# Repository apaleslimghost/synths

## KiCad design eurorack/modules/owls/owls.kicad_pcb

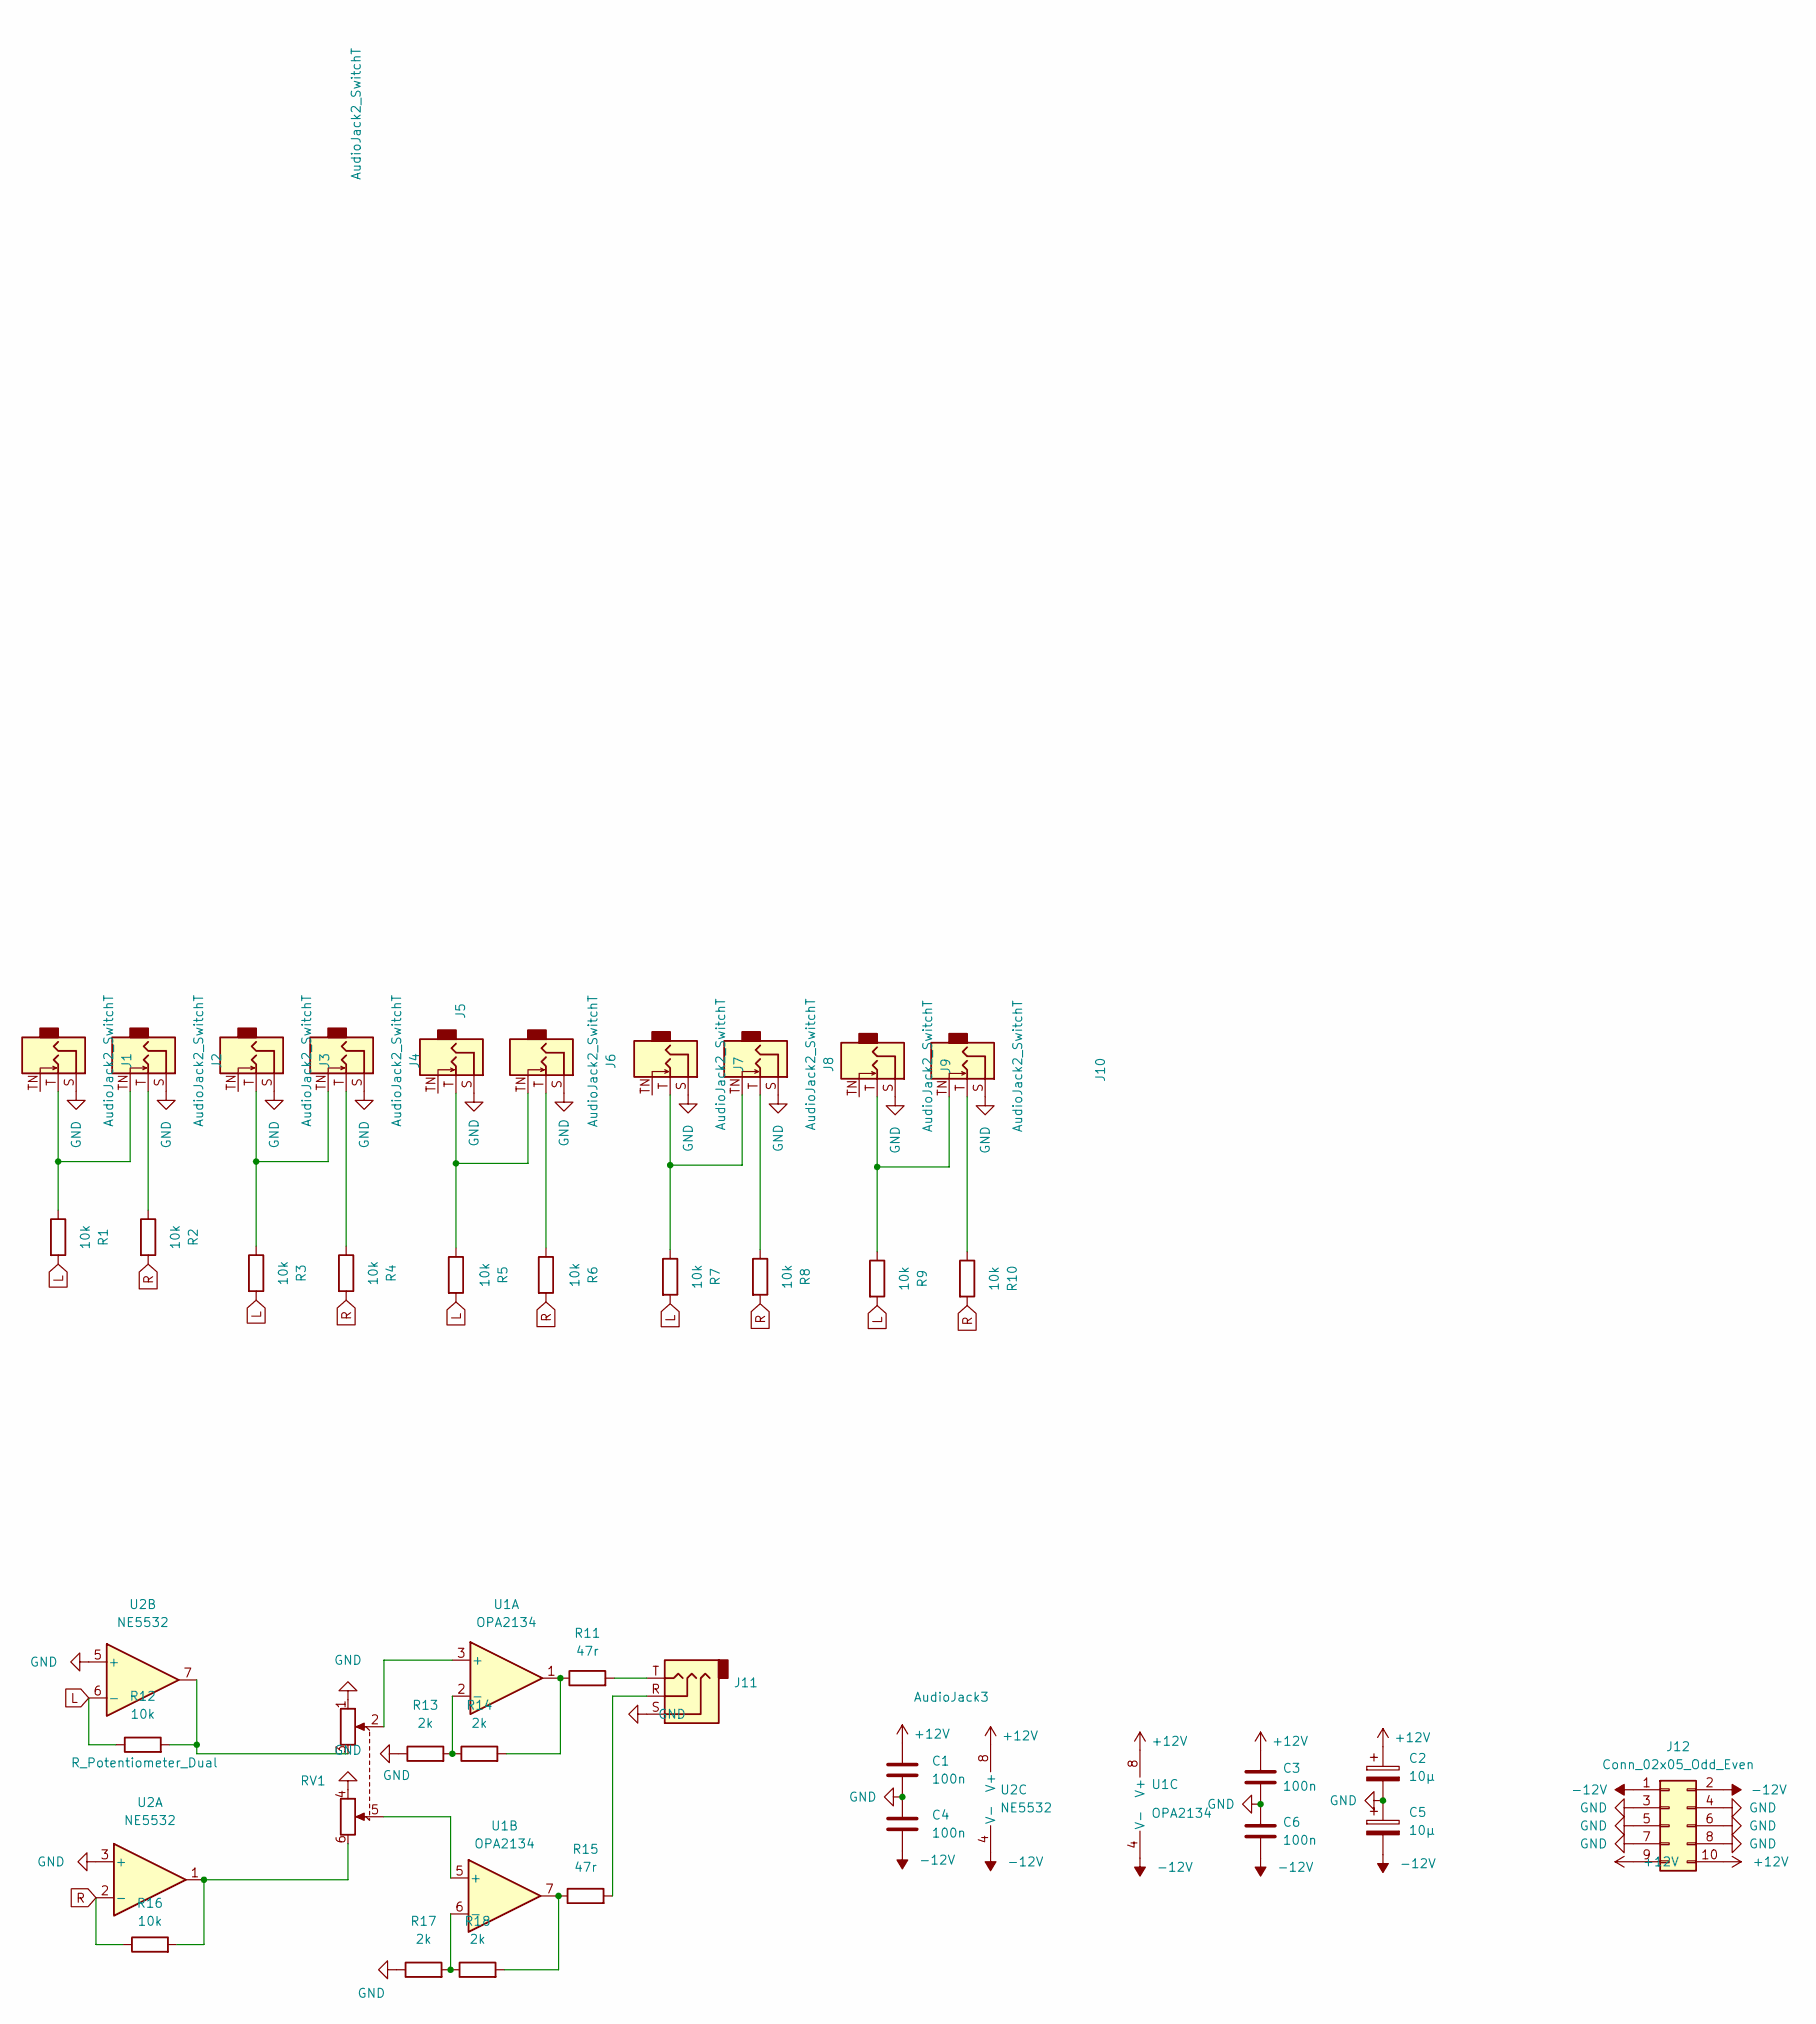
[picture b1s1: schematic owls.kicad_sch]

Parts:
C1, C3, C4, C6: 100n; C_0805_2012Metric_Pad1.18x1.45mm_HandSolder
C2, C5: 10μ; CP_Elec_5x4.5
J1, J2, J3, J4, J5, J6, J7, J8, J9, J10: AudioJack2_SwitchT; Jack_3.5mm_QingPu_WQP-PJ398SM_Vertical
J11: AudioJack3; Jack_3.5mm_QingPu_WQP-PJ366ST_Vertical
J12: Conn_02x05_Odd_Even; PinHeader_2x05_P2.54mm_Vertical_SMD
R1, R2, R3, R4, R5, R6, R7, R8, R9, R10, R12, R16: 10k; R_0805_2012Metric_Pad1.20x1.40mm_HandSolder
R11, R15: 47r; R_0805_2012Metric_Pad1.20x1.40mm_HandSolder
R13, R14, R17, R18: 2k; R_0805_2012Metric_Pad1.20x1.40mm_HandSolder
RV1: R_Potentiometer_Dual; Potentiometer_Alpha_RD902F-40-00D_Dual_Vertical
U1: OPA2134; SOIC-8_3.9x4.9mm_P1.27mm
U2: NE5532; SOIC-8_3.9x4.9mm_P1.27mm

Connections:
+12V: C1.1, C2.1, C3.1, J12.9, J12.10, U1.8 (V+), U2.8 (V+)
-12V: C4.2, C5.2, C6.2, J12.1, J12.2, U1.4 (V-), U2.4 (V-)
GND: C1.2, C2.2, C3.2, C4.1, C5.1, C6.1, J1.S, J2.S, J3.S, J4.S, J5.S, J6.S, J7.S, J8.S, J9.S, J10.S, J11.S, J12.3, J12.4, J12.5, J12.6, J12.7, J12.8, R13.1, R17.1, RV1.1, RV1.4, U2.3 (+), U2.5 (+)
L: R1.2, R3.2, R5.2, R7.2, R9.2, R12.1, U2.6 (-)
unnamed: J1.T, J2.TN, R1.1
unnamed: J2.T, R2.1
unnamed: J3.T, J4.TN, R3.1
unnamed: J4.T, R4.1
unnamed: J5.T, J6.TN, R5.1
unnamed: J6.T, R6.1
unnamed: J7.T, J8.TN, R7.1
unnamed: J8.T, R8.1
unnamed: J10.T, R10.1
unnamed: J9.T, J10.TN, R9.1
unnamed: J11.R, R15.2
unnamed: J11.T, R11.2
unnamed: R11.1, R14.2, U1.1
unnamed: R12.2, RV1.3, U2.7
unnamed: R13.2, R14.1, U1.2 (-)
unnamed: R15.1, R18.2, U1.7
unnamed: R16.2, RV1.6, U2.1
unnamed: R17.2, R18.1, U1.6 (-)
unnamed: RV1.2, U1.3 (+)
unnamed: RV1.5, U1.5 (+)
R: R2.2, R4.2, R6.2, R8.2, R10.2, R16.1, U2.2 (-)

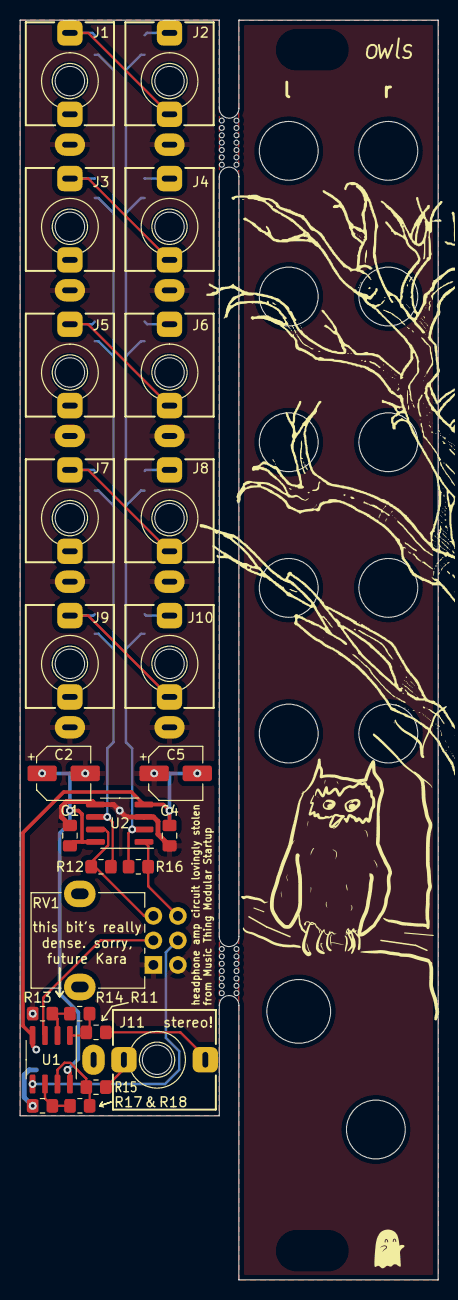
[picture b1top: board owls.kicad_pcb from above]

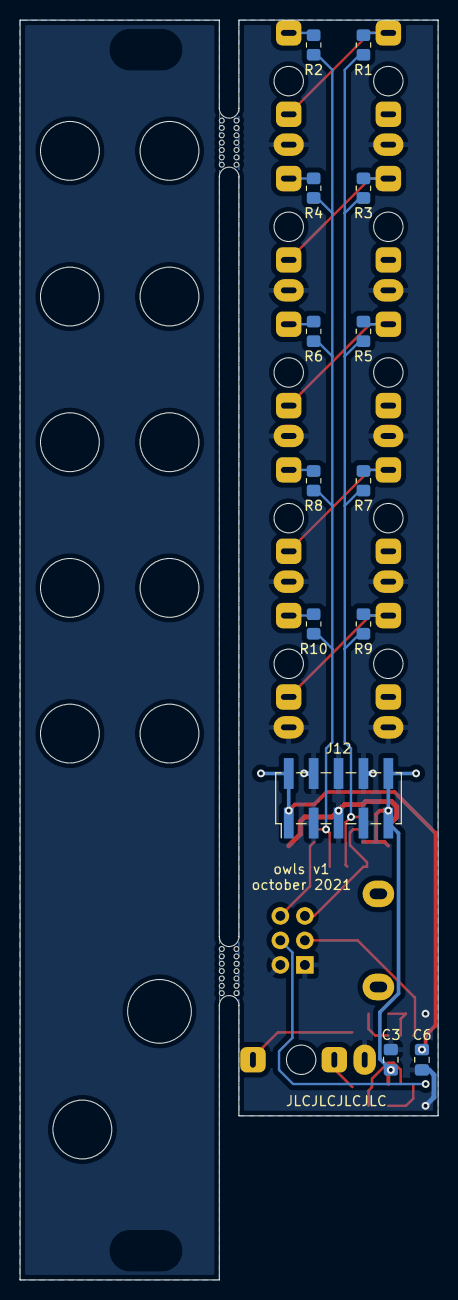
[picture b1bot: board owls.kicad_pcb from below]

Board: 2 copper layers, 42.6 x 128.5 mm, 41 parts (13 on the bottom side), 25 nets.

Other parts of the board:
mouse-bite-2mm-slot, mouse-bite-2mm-slot#2: VAL**; mousebite-2x5mm

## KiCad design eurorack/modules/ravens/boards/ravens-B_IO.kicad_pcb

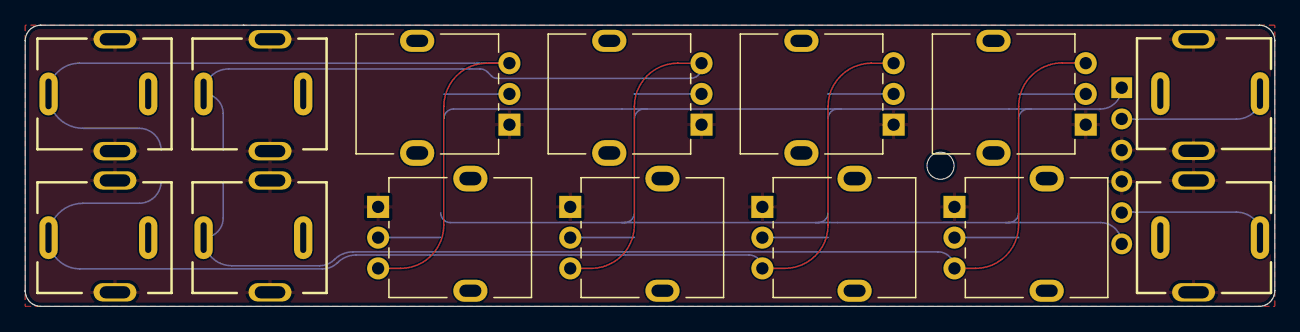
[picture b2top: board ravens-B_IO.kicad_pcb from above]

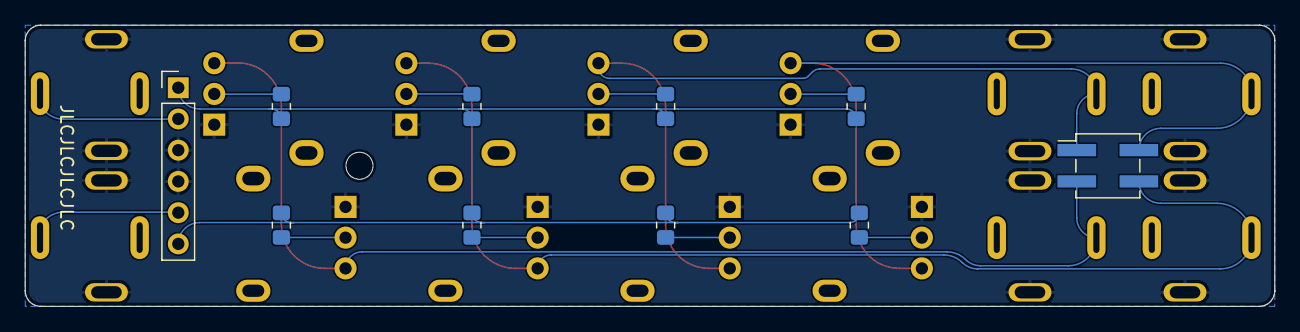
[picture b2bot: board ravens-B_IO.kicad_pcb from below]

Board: 2 copper layers, 101.6 x 22.9 mm, 26 parts (10 on the bottom side), 17 nets.

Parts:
B_IO: Board
H1: MountingHole; MountingHole_2.2mm_M2
J2, J3, J4, J5, J6, J7: AudioJack2_SwitchT; Jack_3.5mm_QingPu_WQP-PJ301BM_Vertical
J8: Conn_01x06_Pin; PinHeader_1x06_P2.54mm_Vertical
J12: Conn_01x04_Pin; PinHeader_2x02_P2.54mm_Vertical_SMD
R1, R2, R3, R4, R5, R6, R7, R8: 100k; R_0805_2012Metric_Pad1.20x1.40mm_HandSolder
RV1, RV2, RV3, RV4, RV5, RV6, RV7, RV8: R_Potentiometer; Potentiometer_Alpha_RD901F-40-00D_Single_Vertical

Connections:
Board_0-Bus A front: J8.1, R1.2, R3.2, R5.2, R7.2
Board_0-Bus B front: J8.6, R2.2, R4.2, R6.2, R8.2
Board_0-GND: J2.S, J3.S, J4.S, J5.S, J6.S, J7.S, J8.3, J8.4, RV1.1, RV2.1, RV3.1, RV4.1, RV5.1, RV6.1, RV7.1, RV8.1
Board_0-In 1: J2.T, J12.2, RV1.3, RV2.3
Board_0-In 2: J3.T, J12.1, RV3.3, RV4.3
Board_0-In 3: J4.T, J12.4, RV5.3, RV6.3
Board_0-In 4: J5.T, J12.3, RV7.3, RV8.3
Board_0-Net-(R1-Pad1): R1.1, RV1.2
Board_0-Net-(R2-Pad1): R2.1, RV2.2
Board_0-Net-(R3-Pad1): R3.1, RV3.2
Board_0-Net-(R4-Pad1): R4.1, RV4.2
Board_0-Net-(R5-Pad1): R5.1, RV5.2
Board_0-Net-(R6-Pad1): R6.1, RV6.2
Board_0-Net-(R7-Pad1): R7.1, RV7.2
Board_0-Net-(R8-Pad1): R8.1, RV8.2
Board_0-Out A front: J6.T, J8.2
Board_0-Out B front: J7.T, J8.5

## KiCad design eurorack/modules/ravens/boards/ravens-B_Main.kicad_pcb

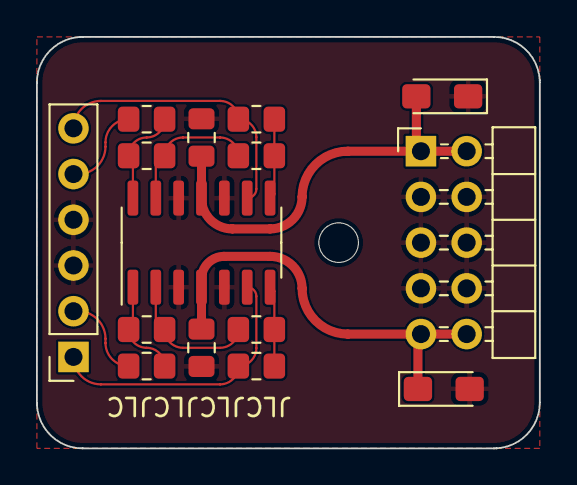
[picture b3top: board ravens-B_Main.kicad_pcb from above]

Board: 2 copper layers, 27.9 x 22.9 mm, 17 parts (0 on the bottom side), 13 nets.

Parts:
B_Main: Board
C1, C2: C_Polarized; CP_EIA-3216-18_Kemet-A_Pad1.58x1.35mm_HandSolder
C3, C4: C; C_0805_2012Metric_Pad1.18x1.45mm_HandSolder
H2: MountingHole; MountingHole_2.2mm_M2
J1: Conn_02x05_Odd_Even; PinHeader_2x05_P2.54mm_Horizontal
J9: Conn_01x06_Socket; PinSocket_1x06_P2.54mm_Vertical
R9, R10, R11, R14, R15, R16: 100k; R_0805_2012Metric_Pad1.20x1.40mm_HandSolder
R12, R13: 1k; R_0805_2012Metric_Pad1.20x1.40mm_HandSolder
U1: TL074; SOIC-14_3.9x8.7mm_P1.27mm

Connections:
Board_0-+12V: C1.1, C3.1, J1.9, J1.10, U1.4 (V+)
Board_0--12V: C2.2, C4.2, J1.1, J1.2, U1.11 (V-)
Board_0-Bus A back: J9.1, R9.1, U1.6 (-)
Board_0-Bus B back: J9.6, R16.1, U1.9 (-)
Board_0-GND1: C1.2, C2.1, C3.2, C4.1, J1.3, J1.4, J1.5, J1.6, J1.7, J1.8, J9.3, J9.4, U1.3 (+), U1.5 (+), U1.10 (+), U1.12 (+)
Board_0-Net-(R10-Pad1): R9.2, R10.1, U1.7
Board_0-Net-(R11-Pad2): R11.2, R12.1, U1.1
Board_0-Net-(R13-Pad1): R13.1, R15.2, U1.14
Board_0-Net-(R14-Pad1): R14.1, R16.2, U1.8
Board_0-Net-(U1A--): R10.2, R11.1, U1.2 (-)
Board_0-Net-(U1D--): R14.2, R15.1, U1.13 (-)
Board_0-Out A back: J9.2, R12.2
Board_0-Out B back: J9.5, R13.2

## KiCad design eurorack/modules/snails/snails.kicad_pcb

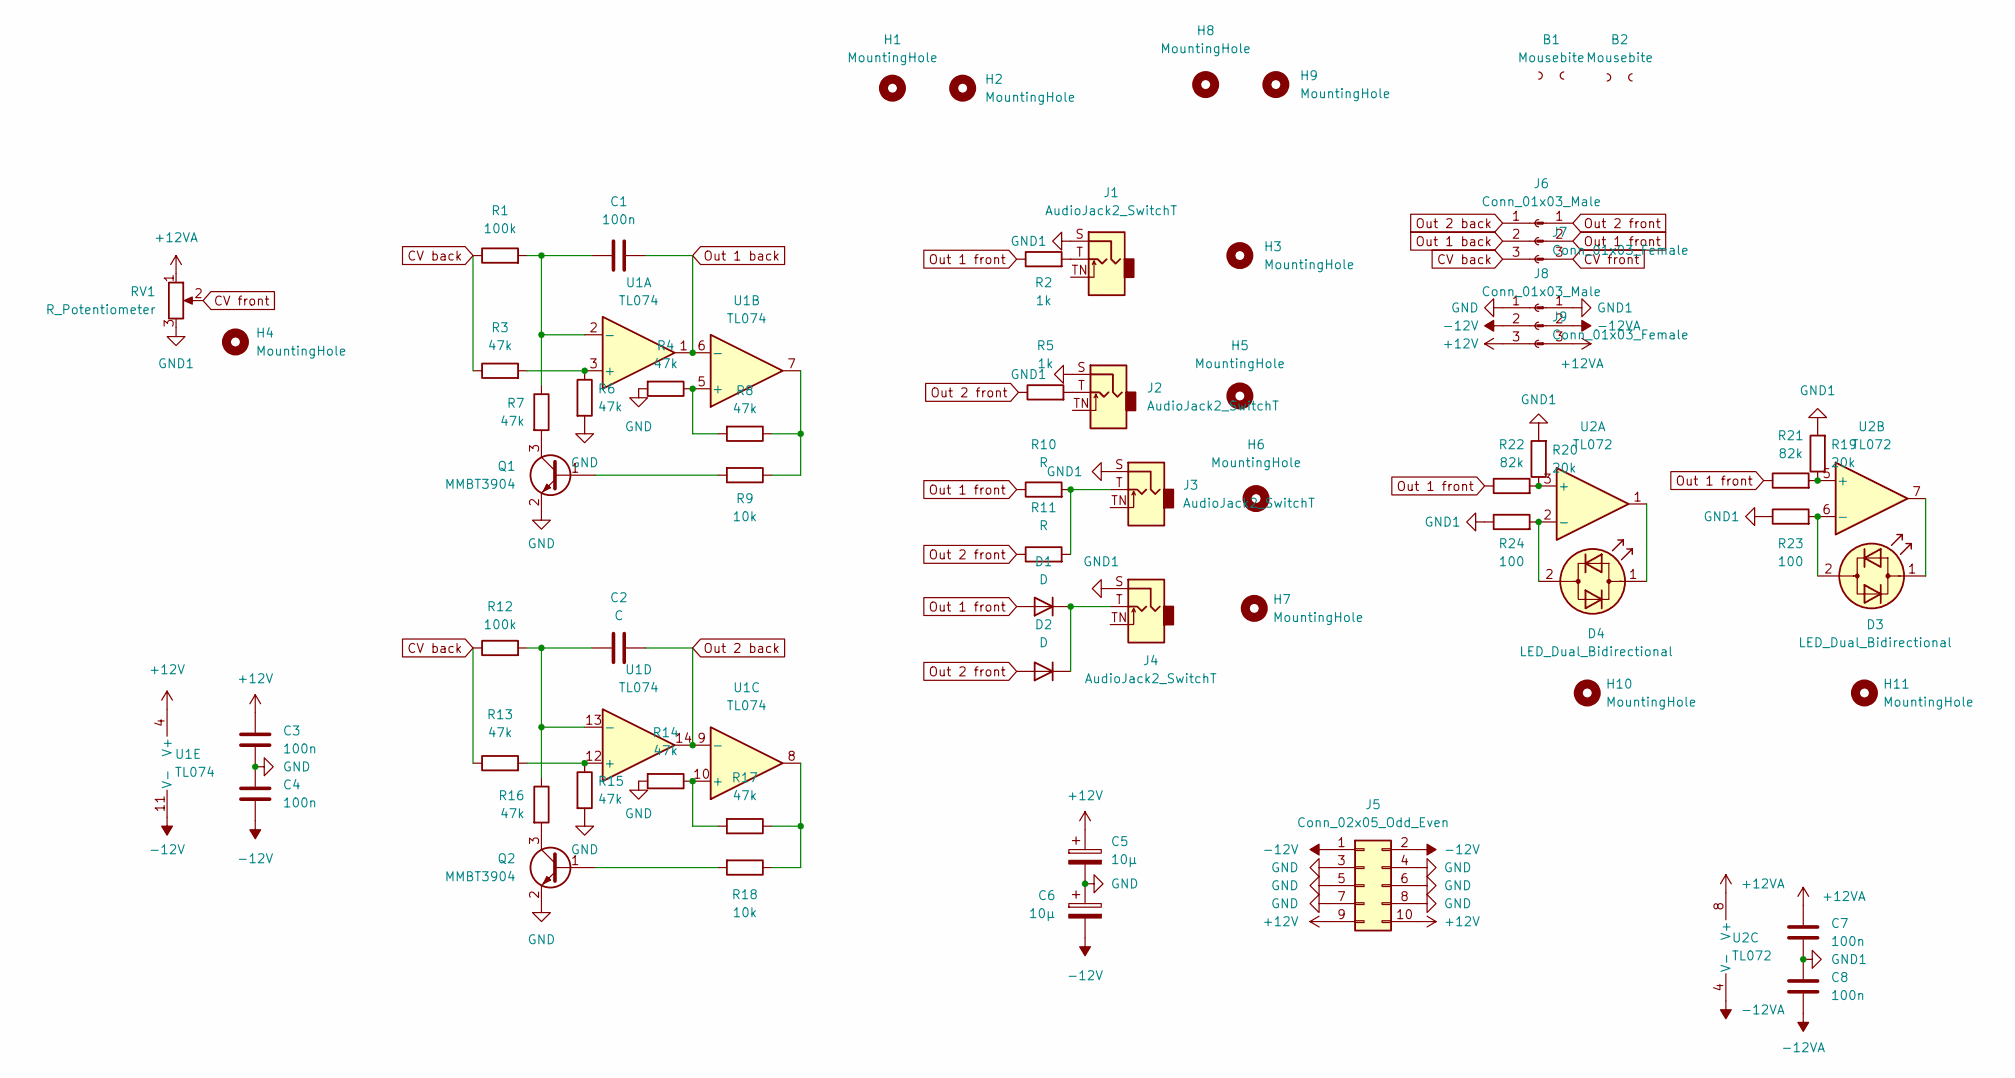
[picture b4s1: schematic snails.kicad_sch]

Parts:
B1, B2: Mousebite; mousebite-2.54x5.08mm
C1, C3, C4, C7, C8: 100n; C_0805_2012Metric_Pad1.18x1.45mm_HandSolder
C2: C; C_0805_2012Metric_Pad1.18x1.45mm_HandSolder
C5, C6: 10μ; CP_Elec_5x5.9
D1, D2: D; D_0805_2012Metric_Pad1.15x1.40mm_HandSolder
D3, D4: LED_Dual_Bidirectional; LED_D3.0mm_FlatTop
H1, H2: MountingHole; MountingHole_2.2mm_M2
H3, H5, H6, H7: MountingHole; hole 6mm (jack panel)
H4: MountingHole; hole 6.5mm (potentiometer panel)
H8, H9: MountingHole; eurorack panel mounting slot
H10, H11: MountingHole; hole 3mm (below jack)
J1, J2, J3, J4: AudioJack2_SwitchT; Jack_3.5mm_QingPu_WQP-PJ301BM_Vertical
J5: Conn_02x05_Odd_Even; PinHeader_2x05_P2.54mm_Vertical
J6, J8: Conn_01x03_Male; PinHeader_1x03_P2.54mm_Vertical
J7, J9: Conn_01x03_Female; PinSocket_1x03_P2.54mm_Vertical
Q1, Q2: MMBT3904; SOT-23
R1, R12: 100k; R_0805_2012Metric_Pad1.20x1.40mm_HandSolder
R2, R5: 1k; R_0805_2012Metric_Pad1.20x1.40mm_HandSolder
R3, R4, R6, R7, R8, R13, R14, R15, R16, R17: 47k; R_0805_2012Metric_Pad1.20x1.40mm_HandSolder
R9, R18: 10k; R_0805_2012Metric_Pad1.20x1.40mm_HandSolder
R10, R11: R; R_0805_2012Metric_Pad1.20x1.40mm_HandSolder
R19, R20: 20k; R_0805_2012Metric_Pad1.20x1.40mm_HandSolder
R21, R22: 82k; R_0805_2012Metric_Pad1.20x1.40mm_HandSolder
R23, R24: 100; R_0805_2012Metric_Pad1.20x1.40mm_HandSolder
RV1: R_Potentiometer; Potentiometer_Alpha_RD901F-40-00D_Single_Vertical
U1: TL074; SOIC-14_3.9x8.7mm_P1.27mm
U2: TL072; SOT-23-8

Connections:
+12V: C3.1, C5.1, J5.9, J5.10, J9.3, U1.4 (V+)
+12VA: C7.1, J8.3, RV1.1, U2.8 (V+)
-12V: C4.2, C6.2, J5.1, J5.2, J9.2, U1.11 (V-)
-12VA: C8.2, J8.2, U2.4 (V-)
CV back: J7.3, R1.1, R3.1, R12.1, R13.1
CV front: J6.3, RV1.2
GND: C3.2, C4.1, C5.2, C6.1, J5.3, J5.4, J5.5, J5.6, J5.7, J5.8, J9.1, Q1.2 (E), Q2.2 (E), R4.2, R6.2, R14.2, R15.2
GND1: C7.2, C8.1, J1.S, J2.S, J3.S, J4.S, J8.1, R19.2, R20.2, R23.1, R24.1, RV1.3
unnamed: C1.1, R1.2, R7.1, U1.2 (-)
unnamed: C2.1, R12.2, R16.1, U1.13 (-)
unnamed: D1.1 (K), D2.1 (K), J4.T
unnamed: D3.1 (KA), U2.7
unnamed: D3.2 (AK), R23.2, U2.6 (-)
unnamed: D4.1 (KA), U2.1
unnamed: D4.2 (AK), R24.2, U2.2 (-)
unnamed: J1.T, R2.2
unnamed: J2.T, R5.2
unnamed: J3.T, R10.2, R11.2
unnamed: Q1.1 (B), R9.2
unnamed: Q1.3 (C), R7.2
unnamed: Q2.1 (B), R18.2
unnamed: Q2.3 (C), R16.2
unnamed: R3.2, R6.1, U1.3 (+)
unnamed: R4.1, R8.2, U1.5 (+)
unnamed: R8.1, R9.1, U1.7
unnamed: R13.2, R15.1, U1.12 (+)
unnamed: R14.1, R17.2, U1.10 (+)
unnamed: R17.1, R18.1, U1.8
unnamed: R19.1, R21.2, U2.5 (+)
unnamed: R20.1, R22.2, U2.3 (+)
Out 1 back: C1.2, J7.2, U1.1, U1.6 (-)
Out 1 front: D1.2 (A), J6.2, R2.1, R10.1, R21.1, R22.1
Out 2 back: C2.2, J7.1, U1.9 (-), U1.14
Out 2 front: D2.2 (A), J6.1, R5.1, R11.1

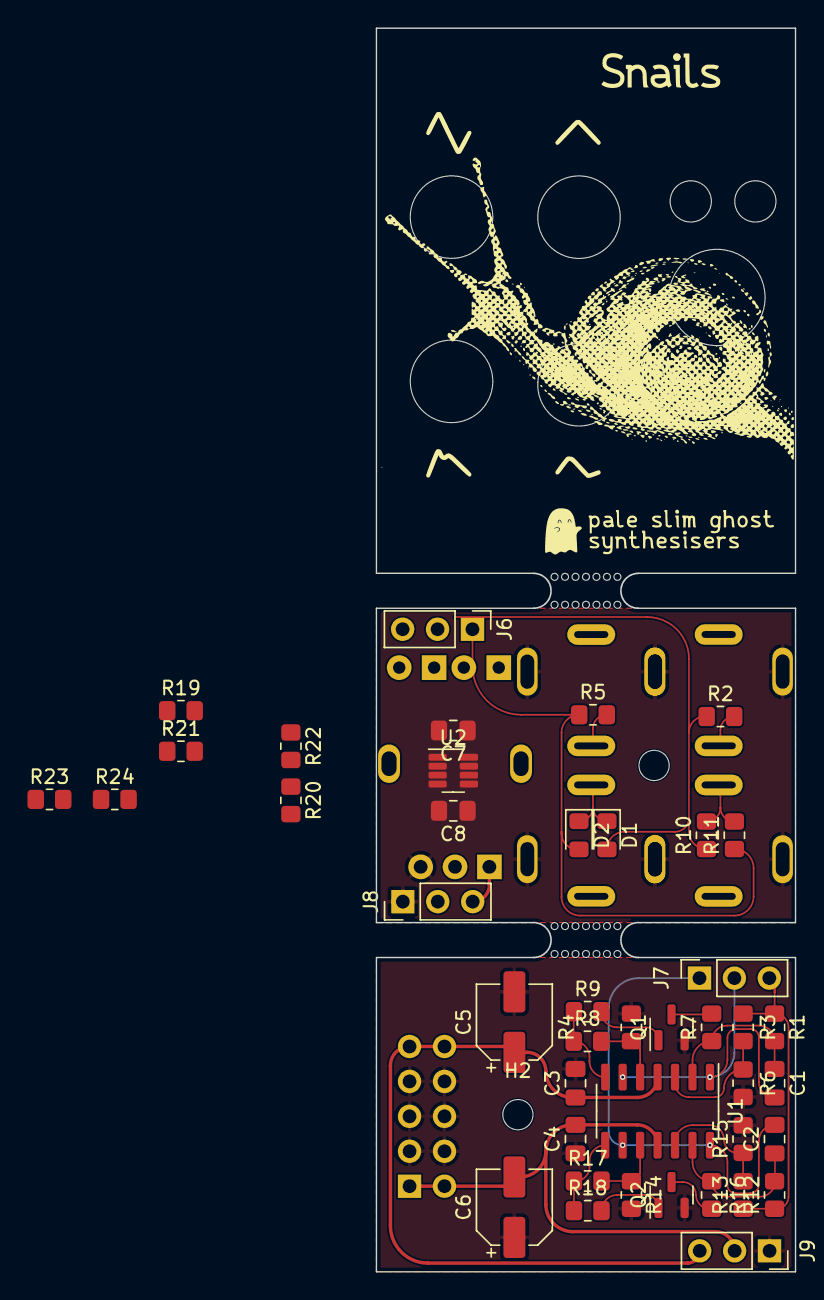
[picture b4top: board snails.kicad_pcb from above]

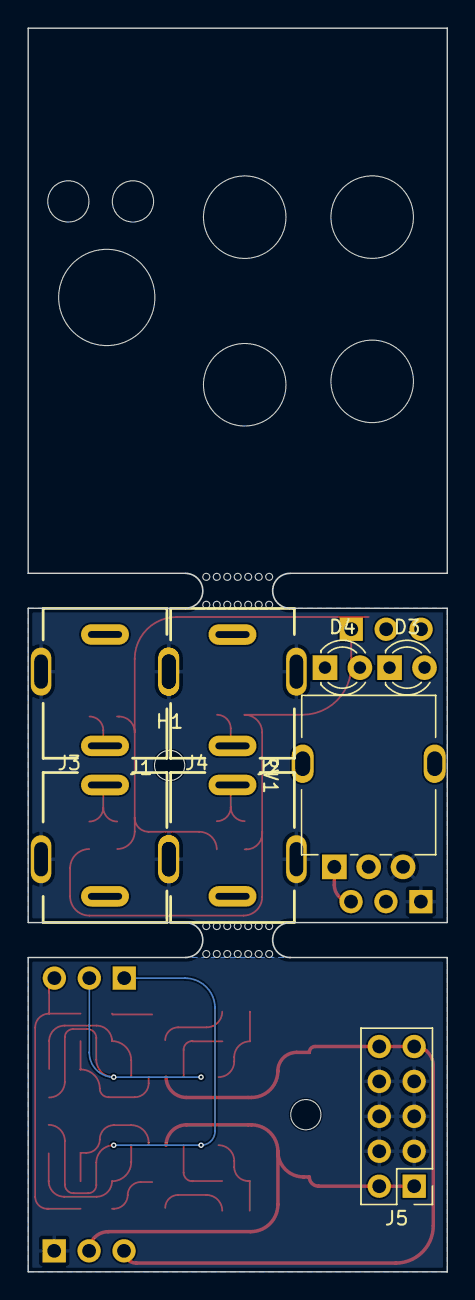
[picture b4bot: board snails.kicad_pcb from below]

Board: 2 copper layers, 30.5 x 90.4 mm, 63 parts (12 on the bottom side), 34 nets.

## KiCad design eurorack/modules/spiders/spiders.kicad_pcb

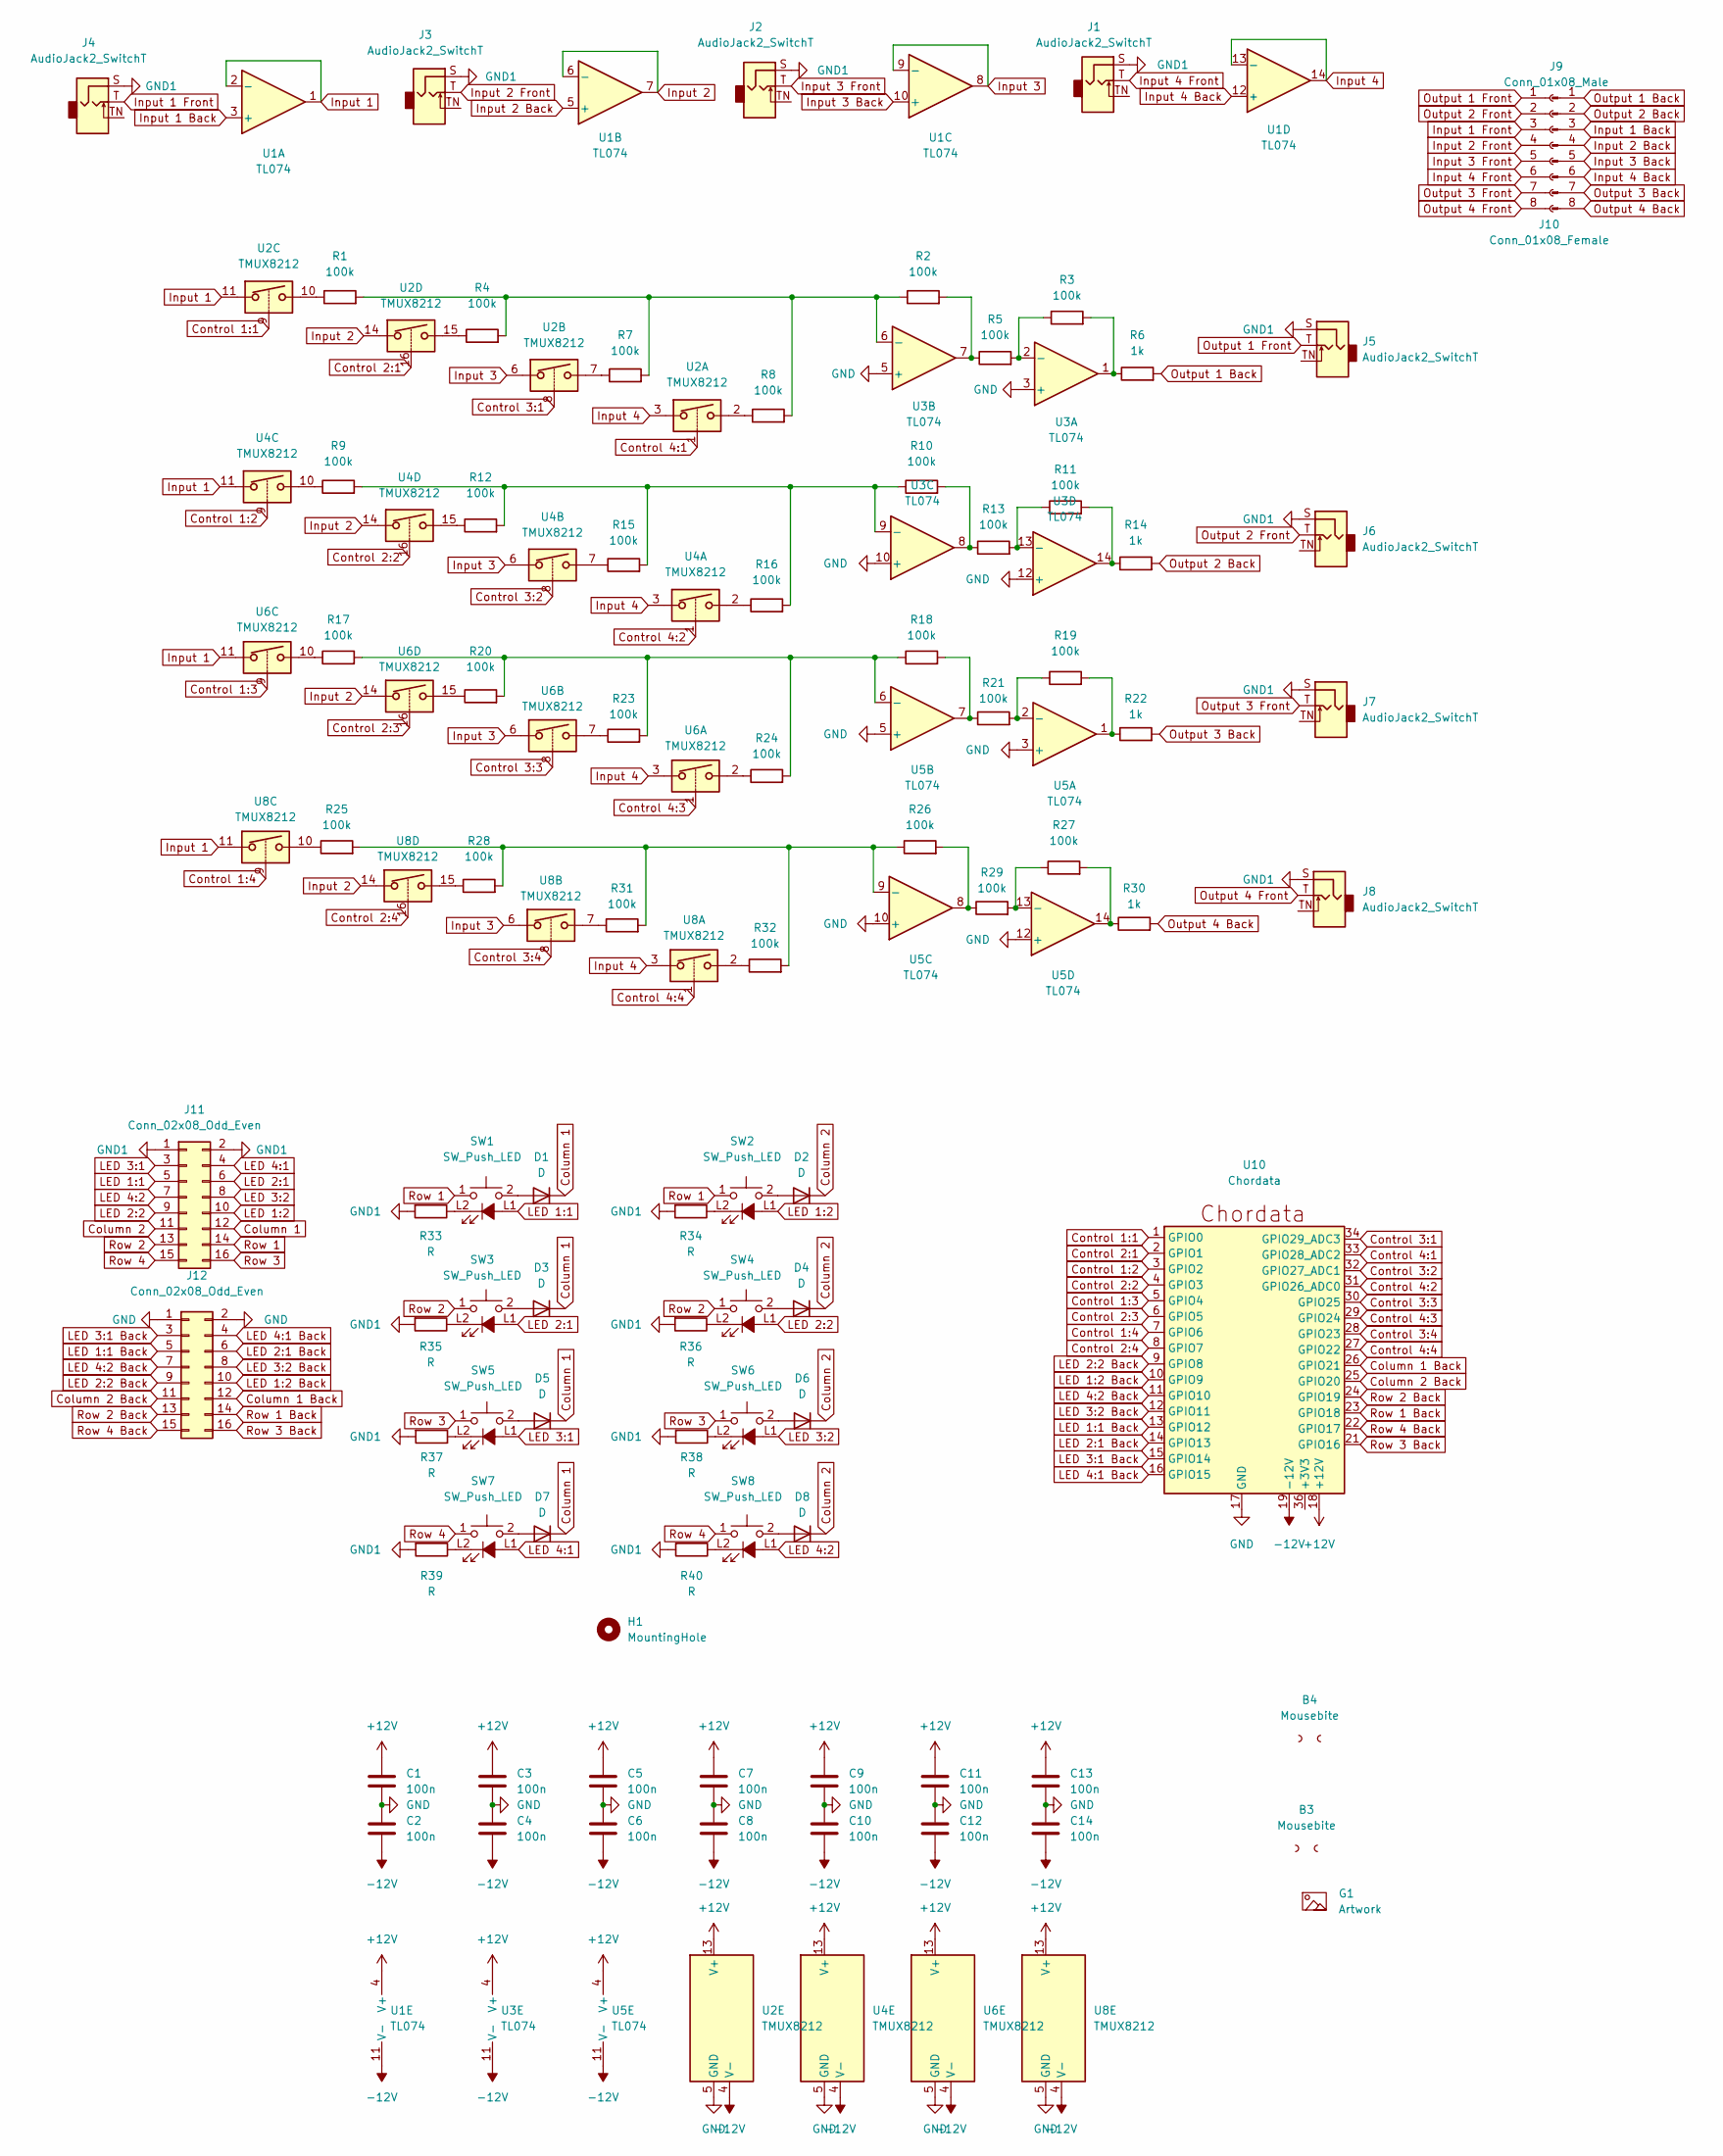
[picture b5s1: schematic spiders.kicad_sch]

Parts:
B3, B4: Mousebite; mousebite-2.54x5.08mm
C1, C2, C3, C4, C5, C6, C7, C8, C9, C10, C11, C12, C13, C14: 100n; C_0805_2012Metric
D1, D2, D3, D4, D5, D6, D7, D8: D; D_SOD-323_HandSoldering
G1: Artwork
H1: MountingHole; MountingHole_2.2mm_M2
J1, J2, J3, J4, J5, J6, J7, J8: AudioJack2_SwitchT; Jack_3.5mm_QingPu_WQP-PJ398SM_Vertical
J9: Conn_01x08_Male; PinHeader_1x08_P2.54mm_Vertical
J10: Conn_01x08_Female; PinSocket_1x08_P2.54mm_Vertical
J11: Conn_02x08_Odd_Even; PinSocket_2x08_P2.54mm_Vertical
J12: Conn_02x08_Odd_Even; PinHeader_2x08_P2.54mm_Vertical
R1, R2, R3, R4, R5, R7, R8, R9, R10, R11, R12, R13, R15, R16, R17, R18, R19, R20, R21, R23, R24, R25, R26, R27, R28, R29, R31, R32: 100k; R_0805_2012Metric
R6, R14, R22, R30: 1k; R_0805_2012Metric
R33, R34, R35, R36, R37, R38, R39, R40: R; R_0805_2012Metric
SW1, SW2, SW3, SW4, SW5, SW6, SW7, SW8: SW_Push_LED; PB01-109TL
U1, U3, U5: TL074; TSOT-23-14
U2, U4, U6, U8: TMUX8212; TSSOP-16_4.4x5mm_P0.65mm
U10: Chordata

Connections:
+12V: C1.1, C3.1, C5.1, C7.1, C9.1, C11.1, C13.1, U1.4 (V+), U2.13 (V+), U3.4 (V+), U4.13 (V+), U5.4 (V+), U6.13 (V+), U8.13 (V+), U10.18 (+12V)
-12V: C2.2, C4.2, C6.2, C8.2, C10.2, C12.2, C14.2, U1.11 (V-), U2.4 (V-), U3.11 (V-), U4.4 (V-), U5.11 (V-), U6.4 (V-), U8.4 (V-), U10.19 (-12V)
Column 1: D1.1 (K), D3.1 (K), D5.1 (K), D7.1 (K), J11.12
Column 1 Back: J12.12, U10.26 (GPIO21)
Column 2: D2.1 (K), D4.1 (K), D6.1 (K), D8.1 (K), J11.11
Column 2 Back: J12.11, U10.25 (GPIO20)
Control 1:1: U2.9, U10.1 (GPIO0)
Control 1:2: U4.9, U10.3 (GPIO2)
Control 1:3: U6.9, U10.5 (GPIO4)
Control 1:4: U8.9, U10.7 (GPIO6)
Control 2:1: U2.16, U10.2 (GPIO1)
Control 2:2: U4.16, U10.4 (GPIO3)
Control 2:3: U6.16, U10.6 (GPIO5)
Control 2:4: U8.16, U10.8 (GPIO7)
Control 3:1: U2.8, U10.34 (GPIO29_ADC3)
Control 3:2: U4.8, U10.32 (GPIO27_ADC1)
Control 3:3: U6.8, U10.30 (GPIO25)
Control 3:4: U8.8, U10.28 (GPIO23)
Control 4:1: U2.1, U10.33 (GPIO28_ADC2)
Control 4:2: U4.1, U10.31 (GPIO26_ADC0)
Control 4:3: U6.1, U10.29 (GPIO24)
Control 4:4: U8.1, U10.27 (GPIO22)
GND: C1.2, C2.1, C3.2, C4.1, C5.2, C6.1, C7.2, C8.1, C9.2, C10.1, C11.2, C12.1, C13.2, C14.1, J12.1, J12.2, U2.5 (GND), U3.3 (+), U3.5 (+), U3.10 (+), U3.12 (+), U4.5 (GND), U5.3 (+), U5.5 (+), U5.10 (+), U5.12 (+), U6.5 (GND), U8.5 (GND), U10.17 (GND), U10.20 (GND), U10.35 (GND)
GND1: J1.S, J2.S, J3.S, J4.S, J5.S, J6.S, J7.S, J8.S, J11.1, J11.2, R33.2, R34.2, R35.2, R36.2, R37.2, R38.2, R39.2, R40.2
Input 1: U1.1, U1.2 (-), U2.11, U4.11, U6.11, U8.11
Input 1 Back: J9.3, U1.3 (+)
Input 1 Front: J4.T, J10.3
Input 2: U1.6 (-), U1.7, U2.14, U4.14, U6.14, U8.14
Input 2 Back: J9.4, U1.5 (+)
Input 2 Front: J3.T, J10.4
Input 3: U1.8, U1.9 (-), U2.6, U4.6, U6.6, U8.6
Input 3 Back: J9.5, U1.10 (+)
Input 3 Front: J2.T, J10.5
Input 4: U1.13 (-), U1.14, U2.3, U4.3, U6.3, U8.3
Input 4 Back: J9.6, U1.12 (+)
Input 4 Front: J1.T, J10.6
LED 1:1: J11.5, SW1.L1 (A)
LED 1:1 Back: J12.5, U10.13 (GPIO12)
LED 1:2: J11.10, SW2.L1 (A)
LED 1:2 Back: J12.10, U10.10 (GPIO9)
LED 2:1: J11.6, SW3.L1 (A)
LED 2:1 Back: J12.6, U10.14 (GPIO13)
LED 2:2: J11.9, SW4.L1 (A)
LED 2:2 Back: J12.9, U10.9 (GPIO8)
LED 3:1: J11.3, SW5.L1 (A)
LED 3:1 Back: J12.3, U10.15 (GPIO14)
LED 3:2: J11.8, SW6.L1 (A)
LED 3:2 Back: J12.8, U10.12 (GPIO11)
LED 4:1: J11.4, SW7.L1 (A)
LED 4:1 Back: J12.4, U10.16 (GPIO15)
LED 4:2: J11.7, SW8.L1 (A)
LED 4:2 Back: J12.7, U10.11 (GPIO10)
unnamed: D1.2 (A), SW1.2
unnamed: D2.2 (A), SW2.2
unnamed: D3.2 (A), SW3.2
unnamed: D4.2 (A), SW4.2
unnamed: D5.2 (A), SW5.2
unnamed: D6.2 (A), SW6.2
unnamed: D7.2 (A), SW7.2
unnamed: D8.2 (A), SW8.2
unnamed: R1.1, U2.10
unnamed: R2.2, R5.1, U3.7
unnamed: R3.2, R6.1, U3.1
unnamed: R4.1, U2.15
unnamed: R7.1, U2.7
unnamed: R8.1, U2.2
unnamed: R9.1, U4.10
unnamed: R10.2, R13.1, U3.8
unnamed: R11.2, R14.1, U3.14
unnamed: R12.1, U4.15
unnamed: R15.1, U4.7
unnamed: R16.1, U4.2
unnamed: R17.1, U6.10
unnamed: R18.2, R21.1, U5.7
unnamed: R19.2, R22.1, U5.1
unnamed: R20.1, U6.15
unnamed: R23.1, U6.7
unnamed: R24.1, U6.2
unnamed: R25.1, U8.10
unnamed: R26.2, R29.1, U5.8
unnamed: R27.2, R30.1, U5.14
unnamed: R28.1, U8.15
unnamed: R31.1, U8.7
unnamed: R32.1, U8.2
unnamed: R33.1, SW1.L2 (K)
unnamed: R34.1, SW2.L2 (K)
unnamed: R35.1, SW3.L2 (K)
unnamed: R36.1, SW4.L2 (K)
unnamed: R37.1, SW5.L2 (K)
unnamed: R38.1, SW6.L2 (K)
unnamed: R39.1, SW7.L2 (K)
unnamed: R40.1, SW8.L2 (K)
unnamed: R3.1, R5.2, U3.2 (-)
unnamed: R1.2, R2.1, R4.2, R7.2, R8.2, U3.6 (-)
unnamed: R9.2, R10.1, R12.2, R15.2, R16.2, U3.9 (-)
unnamed: R11.1, R13.2, U3.13 (-)
unnamed: R19.1, R21.2, U5.2 (-)
unnamed: R17.2, R18.1, R20.2, R23.2, R24.2, U5.6 (-)
unnamed: R25.2, R26.1, R28.2, R31.2, R32.2, U5.9 (-)
unnamed: R27.1, R29.2, U5.13 (-)
Output 1 Back: J9.1, R6.2
Output 1 Front: J5.T, J10.1
Output 2 Back: J9.2, R14.2
Output 2 Front: J6.T, J10.2
Output 3 Back: J9.7, R22.2
Output 3 Front: J7.T, J10.7
Output 4 Back: J9.8, R30.2
Output 4 Front: J8.T, J10.8
Row 1: J11.14, SW1.1, SW2.1
Row 1 Back: J12.14, U10.23 (GPIO18)
Row 2: J11.13, SW3.1, SW4.1
Row 2 Back: J12.13, U10.24 (GPIO19)
Row 3: J11.16, SW5.1, SW6.1
Row 3 Back: J12.16, U10.21 (GPIO16)
Row 4: J11.15, SW7.1, SW8.1
Row 4 Back: J12.15, U10.22 (GPIO17)

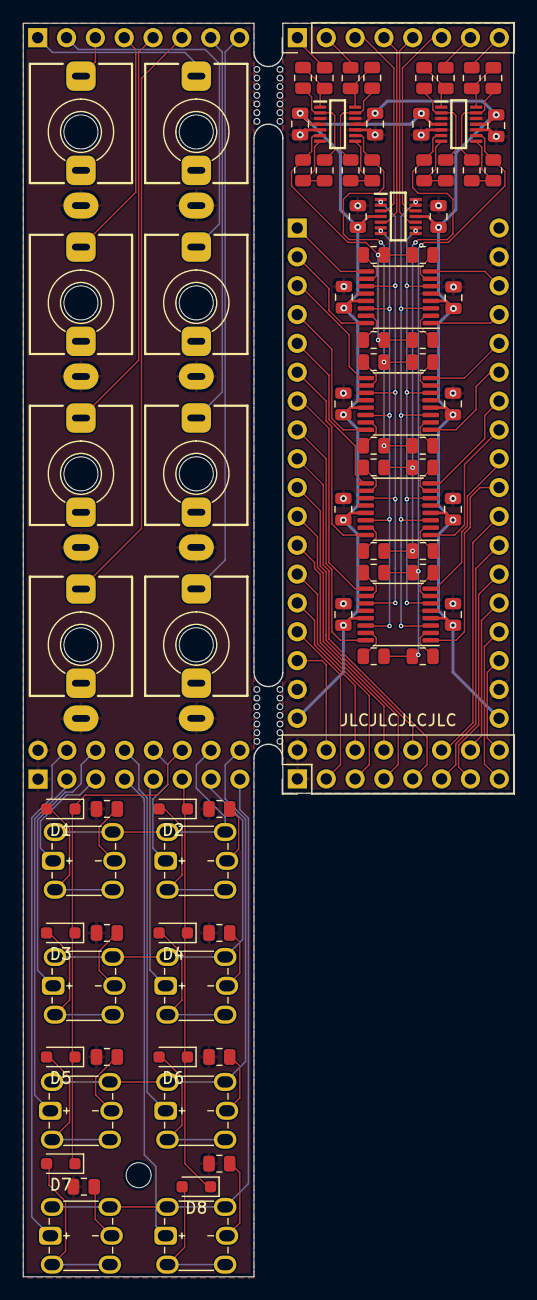
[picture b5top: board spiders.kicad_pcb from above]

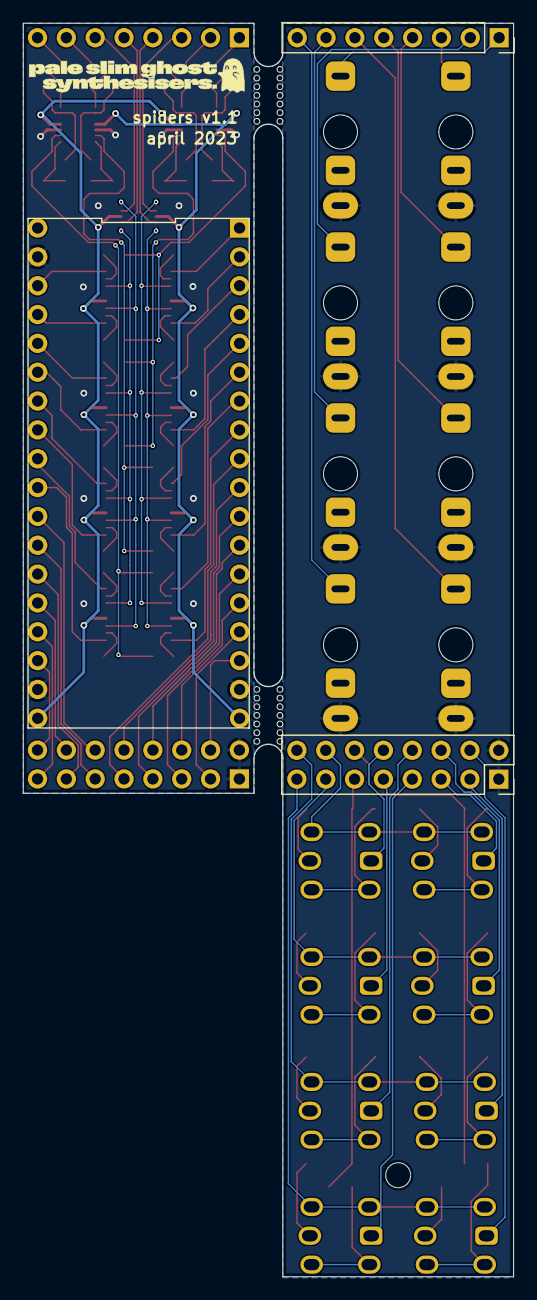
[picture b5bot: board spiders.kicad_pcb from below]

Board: 2 copper layers, 43.2 x 110.4 mm, 93 parts (3 on the bottom side), 116 nets.
